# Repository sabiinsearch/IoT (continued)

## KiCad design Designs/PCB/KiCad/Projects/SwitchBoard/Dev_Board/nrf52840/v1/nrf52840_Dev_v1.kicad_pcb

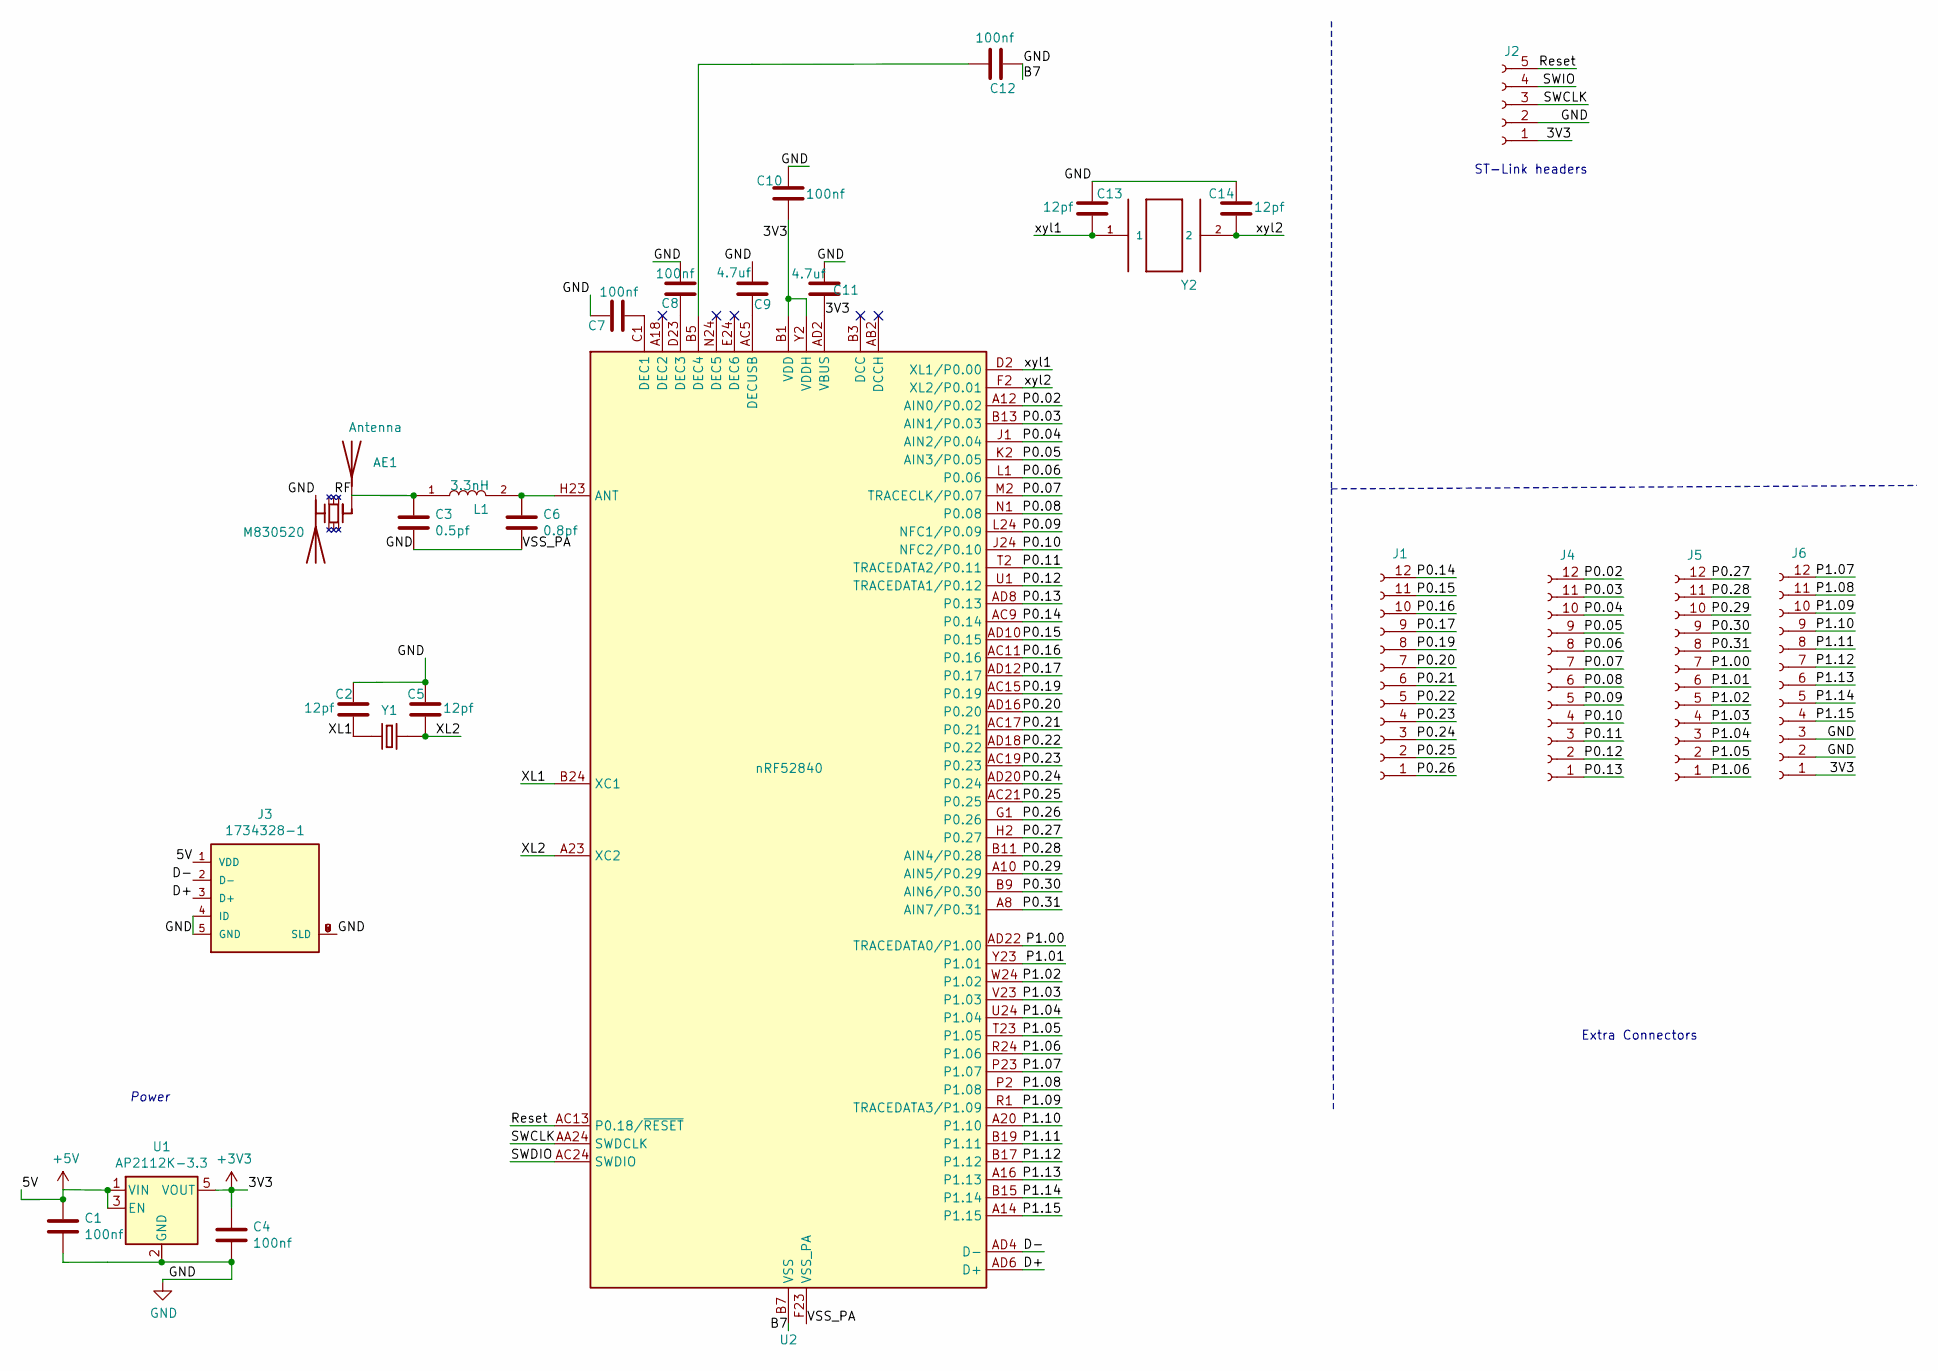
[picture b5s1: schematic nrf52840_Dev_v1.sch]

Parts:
AE1: Antenna; PinHeader_1x01_P2.54mm_Vertical
AE2: M830520
C1, C4, C7, C8, C10, C12: 100nf; C_0805_2012Metric
C2, C5, C13, C14: 12pf; C_0805_2012Metric
C3: 0.5pf; C_0805_2012Metric
C6: 0.8pf; C_0805_2012Metric
C9, C11: 4.7uf; C_0805_2012Metric
J1, J4, J5, J6: Conn_01x12_Female; PinHeader_1x12_P2.54mm_Vertical
J2: Conn_01x05_Female; Pin_Header_Straight_1x05_Pitch2.54mm
J3: 1734328-1; usb_mini_TE_1734328-1
L1: 3.3nH; L_0805_2012Metric
U1: AP2112K-3.3; SOT-23-5
U2: nRF52840; NRF52840-QIAA-R
Y1: ABM7-32.000MHZ-D2Y-T; XTAL_ABM7-32.000MHZ-D2Y-T; PARTREV 08.06.15
Y2: ABS07-32.768KHZ-7-1-T; XTAL320X150X90

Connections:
/3V3: C4.1, C10.1, C11.1, J2.1, J6.1, U1.5 (VOUT), U2.A22 (VDD), U2.AD2 (VBUS), U2.AD14 (VDD), U2.AD23 (VDD), U2.B1 (VDD), U2.W1 (VDD), U2.Y2 (VDDH)
/5V: C1.1, J3.1 (VDD), U1.1 (VIN), U1.3 (EN)
/B7: AE2.2 (PCB_Trace), C1.2, C2.1, C3.2, C4.2, C5.1, C6.2, C7.2, C8.2, C9.2, C10.2, C11.2, C12.1, C13.1, C14.1, J2.2, J3.4 (ID), J3.5 (GND), J3.6 (SLD), J3.7 (SLD), J3.8 (SLD), J3.9 (SLD), J6.2, J6.3, U1.2 (GND), U2.B7 (VSS), U2.EP (VSS), U2.F23 (VSS_PA)
/D+: J3.3 (D+), U2.AD6 (D+)
/D-: J3.2 (D-), U2.AD4 (D-)
/P0.02: J4.12, U2.A12 (AIN0/P0.02)
/P0.03: J4.11, U2.B13 (AIN1/P0.03)
/P0.04: J4.10, U2.J1 (AIN2/P0.04)
/P0.05: J4.9, U2.K2 (AIN3/P0.05)
/P0.06: J4.8, U2.L1 (P0.06)
/P0.07: J4.7, U2.M2 (TRACECLK/P0.07)
/P0.08: J4.6, U2.N1 (P0.08)
/P0.09: J4.5, U2.L24 (NFC1/P0.09)
/P0.10: J4.4, U2.J24 (NFC2/P0.10)
/P0.11: J4.3, U2.T2 (TRACEDATA2/P0.11)
/P0.12: J4.2, U2.U1 (TRACEDATA1/P0.12)
/P0.13: J4.1, U2.AD8 (P0.13)
/P0.14: J1.12, U2.AC9 (P0.14)
/P0.15: J1.11, U2.AD10 (P0.15)
/P0.16: J1.10, U2.AC11 (P0.16)
/P0.17: J1.9, U2.AD12 (P0.17)
/P0.19: J1.8, U2.AC15 (P0.19)
/P0.20: J1.7, U2.AD16 (P0.20)
/P0.21: J1.6, U2.AC17 (P0.21)
/P0.22: J1.5, U2.AD18 (P0.22)
/P0.23: J1.4, U2.AC19 (P0.23)
/P0.24: J1.3, U2.AD20 (P0.24)
/P0.25: J1.2, U2.AC21 (P0.25)
/P0.26: J1.1, U2.G1 (P0.26)
/P0.27: J5.12, U2.H2 (P0.27)
/P0.28: J5.11, U2.B11 (AIN4/P0.28)
/P0.29: J5.10, U2.A10 (AIN5/P0.29)
/P0.30: J5.9, U2.B9 (AIN6/P0.30)
/P0.31: J5.8, U2.A8 (AIN7/P0.31)
/P1.00: J5.7, U2.AD22 (TRACEDATA0/P1.00)
/P1.01: J5.6, U2.Y23 (P1.01)
/P1.02: J5.5, U2.W24 (P1.02)
/P1.03: J5.4, U2.V23 (P1.03)
/P1.04: J5.3, U2.U24 (P1.04)
/P1.05: J5.2, U2.T23 (P1.05)
/P1.06: J5.1, U2.R24 (P1.06)
/P1.07: J6.12, U2.P23 (P1.07)
/P1.08: J6.11, U2.P2 (P1.08)
/P1.09: J6.10, U2.R1 (TRACEDATA3/P1.09)
/P1.10: J6.9, U2.A20 (P1.10)
/P1.11: J6.8, U2.B19 (P1.11)
/P1.12: J6.7, U2.B17 (P1.12)
/P1.13: J6.6, U2.A16 (P1.13)
/P1.14: J6.5, U2.B15 (P1.14)
/P1.15: J6.4, U2.A14 (P1.15)
/RF: AE1.1, AE2.1 (FEED), C3.1, L1.1
/Reset: J2.5, U2.AC13 (P0.18/~RESET)
/SWCLK: J2.3, U2.AA24 (SWDCLK)
/SWDIO: U2.AC24 (SWDIO)
/SWIO: J2.4
/XL1: C2.2, U2.B24 (XC1), Y1.1
/XL2: C5.2, U2.A23 (XC2), Y1.2
/xyl1: C13.2, U2.D2 (XL1/P0.00), Y2.1
/xyl2: C14.2, U2.F2 (XL2/P0.01), Y2.2
unnamed: C6.1, L1.2, U2.H23 (ANT)
unnamed: C7.1, U2.C1 (DEC1)
unnamed: C8.1, U2.D23 (DEC3)
unnamed: C9.1, U2.AC5 (DECUSB)
unnamed: C12.2, U2.B5 (DEC4)

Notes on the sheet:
ST-Link headers
Power
Extra Connectors

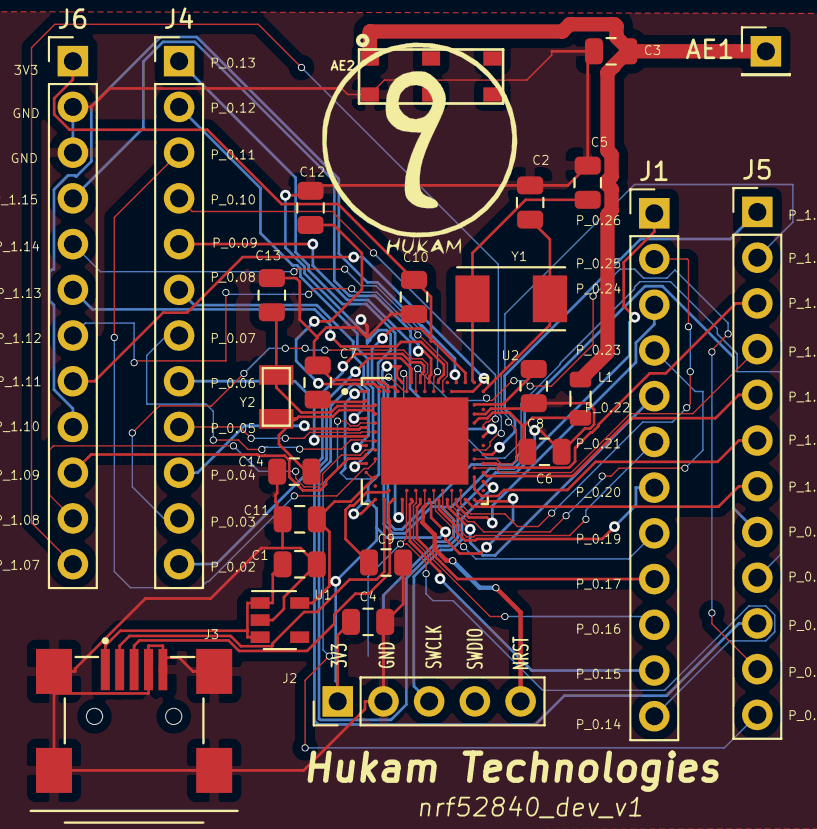
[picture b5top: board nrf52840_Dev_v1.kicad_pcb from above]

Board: 2 copper layers, 27 parts (0 on the bottom side), 62 nets.

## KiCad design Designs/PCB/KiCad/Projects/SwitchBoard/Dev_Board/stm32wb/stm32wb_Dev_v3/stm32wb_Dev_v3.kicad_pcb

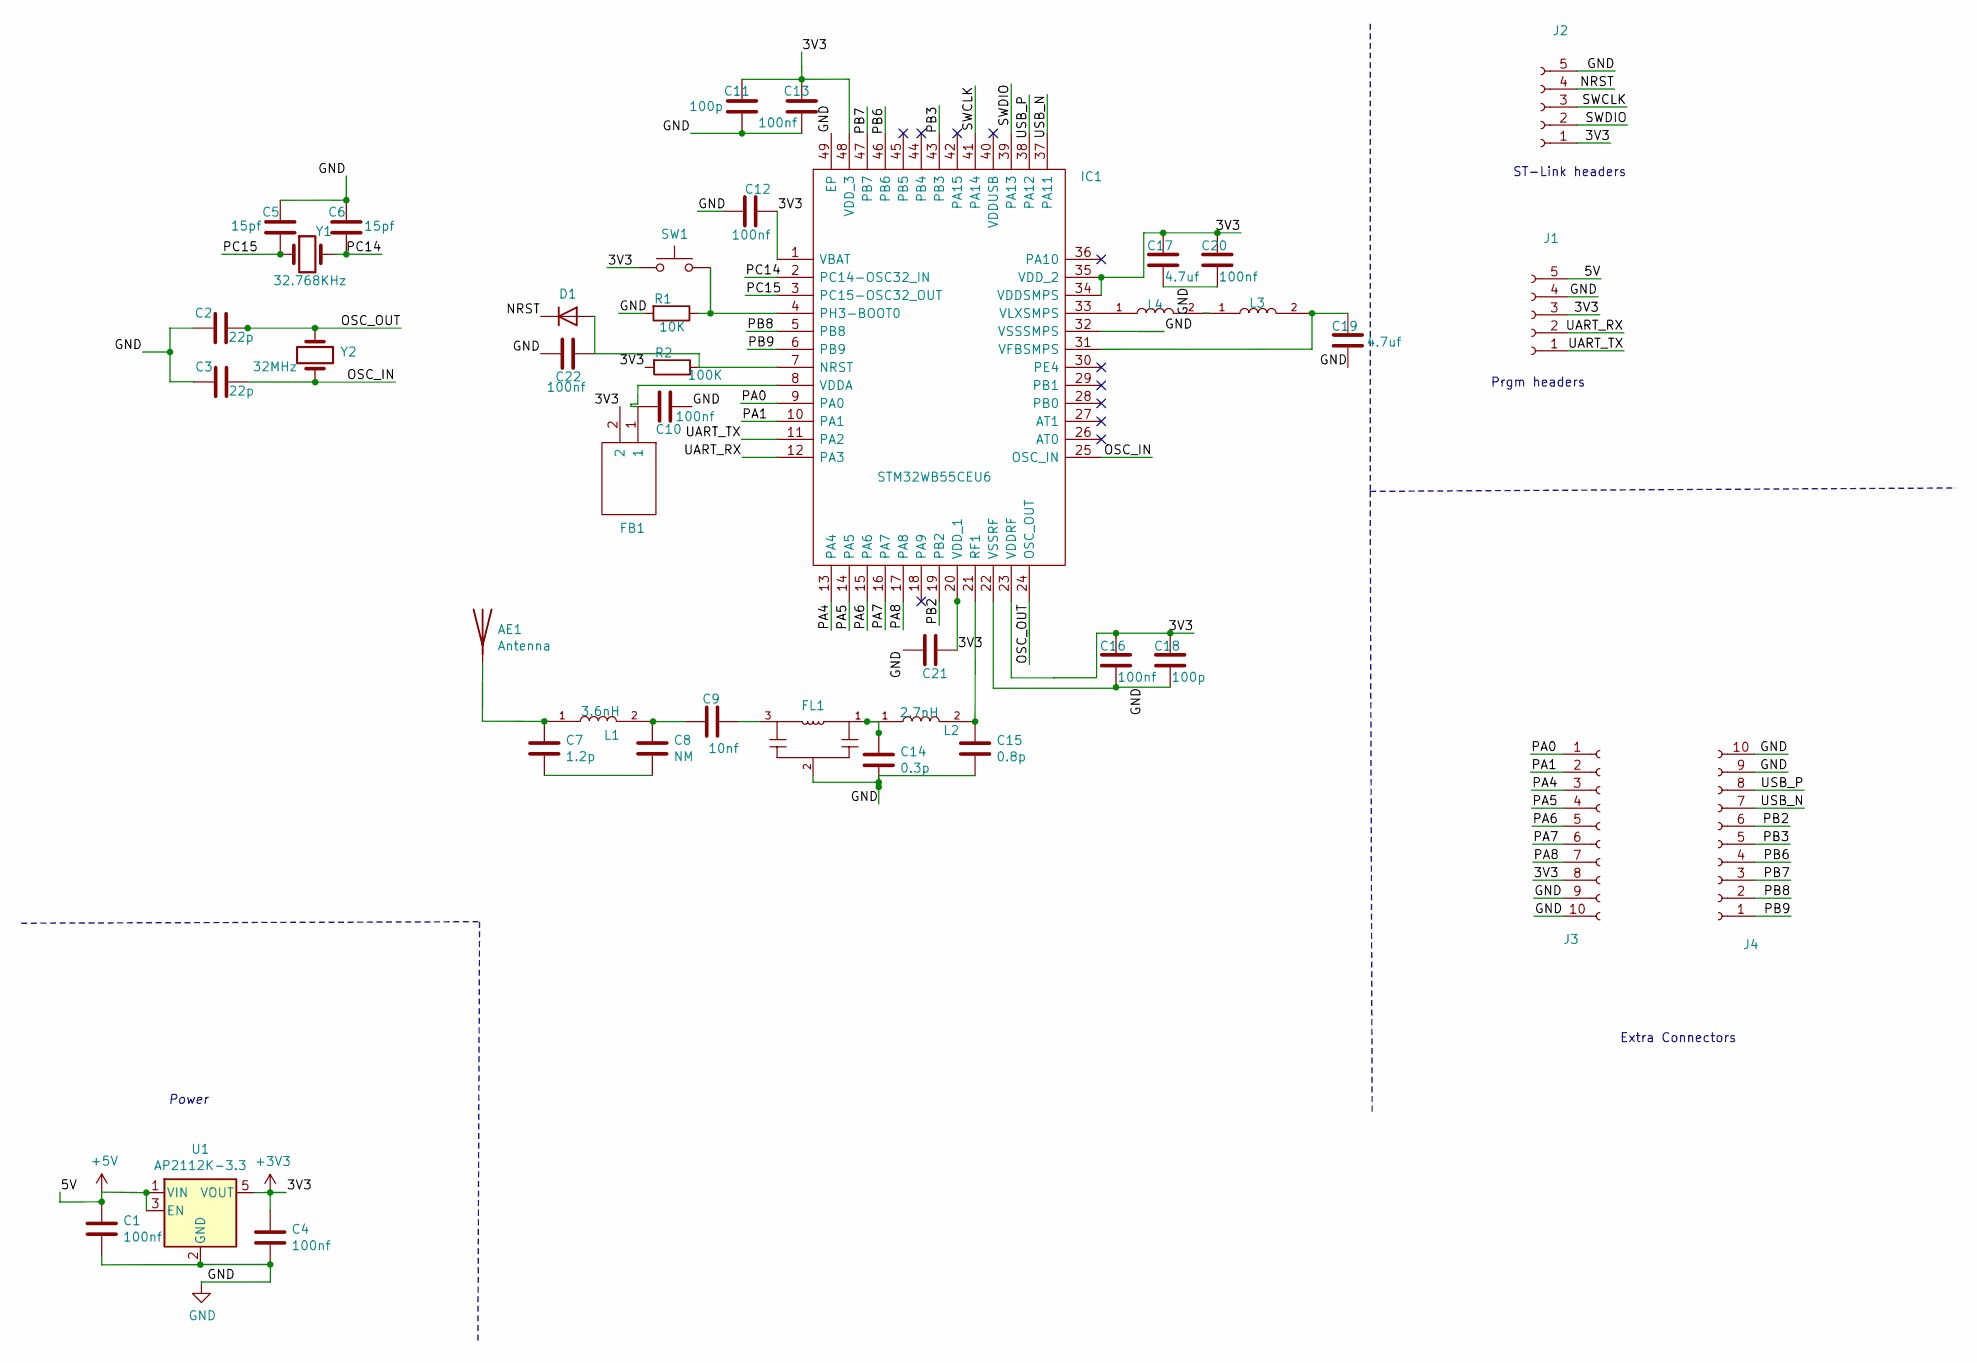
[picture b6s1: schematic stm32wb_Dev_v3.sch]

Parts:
AE1: Antenna; Pin_Header_Straight_1x01_Pitch2.54mm
C1, C4, C10, C12, C13, C16, C20: 100nf; C_0805
C2, C3: 22p; C_0805
C5, C6: 15pf; C_0805
C7: 1.2p; C_0805
C8: NM; C_0805
C9: 10nf; C_0805
C11, C18: 100p; C_0805
C14: 0.3p; C_0805
C15: 0.8p; C_0805
C17, C19: 4.7uf; C_1206_HandSoldering
C21: 100nf; C_0805_2012Metric
C22: 100nf; C_0805_2012Metric_Pad1.18x1.45mm_HandSolder
D1: BAT54K; D_1812_4532Metric
FB1: FCM1608KF-601T03; R_0805_2012Metric_Pad1.20x1.40mm_HandSolder; Manufacturer_Part_Number FCM1608KF-601T03
FL1: LFB182G45CGFD436; CAPC2012X135N
IC1: STM32WB55CEU6; QFN50P700X700X65-49N-D; Manufacturer_Part_Number STM32WB55CEU6; Mouser Part Number 511-STM32WB55CEU6
J1, J2: Conn_01x05_Female; Pin_Header_Straight_1x05_Pitch2.54mm
J3, J4: Conn_01x10_Female; PinHeader_1x10_P2.54mm_Vertical
L1: 3.6nH; L_0805_HandSoldering
L2: 2.7nH; L_0805_HandSoldering
L3: 10uH; L_0805_2012Metric
L4: 10nH; L_0805_2012Metric
R1: 10K; R_0805_2012Metric_Pad1.20x1.40mm_HandSolder
R2: 100K; R_0805_2012Metric_Pad1.20x1.40mm_HandSolder
SW1: SW_Push; SW_SPST_B3U-1000P
U1: AP2112K-3.3; SOT-23-5
Y1: 32.768KHz; Crystal_Round_d3.0mm_Vertical
Y2: 32MHz; Crystal_HC18-U_Vertical

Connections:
/3V3: C4.1, C11.1, C12.1, C13.1, C16.1, C17.1, C18.1, C20.1, C21.1, FB1.2, IC1.1 (VBAT), IC1.20 (VDD_1), IC1.23 (VDDRF), IC1.34 (VDDSMPS), IC1.35 (VDD_2), IC1.48 (VDD_3), J1.3, J2.1, J3.8, R2.2, SW1.1, U1.5 (VOUT)
/5V: C1.1, J1.5, U1.1 (VIN), U1.3 (EN)
/GND: C1.2, C2.2, C3.2, C4.2, C5.1, C6.1, C10.2, C11.2, C12.2, C13.2, C14.2, C15.2, C16.2, C17.2, C18.2, C19.2, C20.2, C21.2, C22.2, FL1.2, IC1.22 (VSSRF), IC1.32 (VSSSMPS), IC1.49 (EP), J1.4, J2.5, J3.9, J3.10, J4.9, J4.10, R1.2, U1.2 (GND)
/NRST: D1.1 (K), J2.4
/OSC_IN: C3.1, IC1.25 (OSC_IN), Y2.2
/OSC_OUT: C2.1, IC1.24 (OSC_OUT), Y2.1
/PA0: IC1.9 (PA0), J3.1
/PA1: IC1.10 (PA1), J3.2
/PA4: IC1.13 (PA4), J3.3
/PA5: IC1.14 (PA5), J3.4
/PA6: IC1.15 (PA6), J3.5
/PA7: IC1.16 (PA7), J3.6
/PA8: IC1.17 (PA8), J3.7
/PB2: IC1.19 (PB2), J4.6
/PB3: IC1.43 (PB3), J4.5
/PB6: IC1.46 (PB6), J4.4
/PB7: IC1.47 (PB7), J4.3
/PB8: IC1.5 (PB8), J4.2
/PB9: IC1.6 (PB9), J4.1
/PC14: C6.2, IC1.2 (PC14-OSC32_IN), Y1.2
/PC15: C5.2, IC1.3 (PC15-OSC32_OUT), Y1.1
/SWCLK: IC1.41 (PA14), J2.3
/SWDIO: IC1.39 (PA13), J2.2
/UART_RX: IC1.12 (PA3), J1.2
/UART_TX: IC1.11 (PA2), J1.1
/USB_N: IC1.37 (PA11), J4.7
/USB_P: IC1.38 (PA12), J4.8
unnamed: AE1.1, C7.1, L1.1
unnamed: C7.2, C8.2
unnamed: C8.1, C9.1, L1.2
unnamed: C9.2, FL1.3
unnamed: C10.1, FB1.1, IC1.8 (VDDA)
unnamed: C14.1, FL1.1, L2.1
unnamed: C15.1, IC1.21 (RF1), L2.2
unnamed: C19.1, IC1.31 (VFBSMPS), L3.2
unnamed: C22.1, D1.2 (A), IC1.7 (NRST), R2.1
unnamed: IC1.4 (PH3-BOOT0), R1.1, SW1.2
unnamed: IC1.33 (VLXSMPS), L4.1
unnamed: L3.1, L4.2

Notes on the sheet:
ST-Link headers
Prgm headers
Power
Extra Connectors

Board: 2 copper layers, 41 parts (24 on the bottom side), 38 nets, no tracks yet.

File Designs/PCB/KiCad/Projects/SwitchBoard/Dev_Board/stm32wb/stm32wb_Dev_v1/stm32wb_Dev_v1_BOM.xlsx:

Id | Designator | Value | Package | Quantity | Supplier and ref
1 | FL1 | LFB182G45CGFD436 | FIL_LFB182G45CGFD436 | 1
2 | IC1 | STM32WB55CEU6 | QFN50P700X700X65-49N-D | 1
3 | C19,C17 | 4.7uf | C_1206_HandSoldering | 2
4 | AE1 | Antenna | Pin_Header_Straight_1x01_Pitch2.54mm | 1
5 | C1,C4,C10,C12,C13,C16,C20 | 100nf | C_0805 | 7
6 | C2,C3 | 22p | C_0805 | 2
7 | C5,C6 | 10p | C_0805 | 2
8 | C7 | 1.2p | C_0805 | 1
9 | C8 | NM | C_0805 | 1
10 | C9 | 10nf | C_0805 | 1 |  |  |  | Available
11 | C11,C18 | 100p | C_0805 | 2 |  |  |  | Not Available
12 | C14 | 0.3p | C_0805 | 1
13 | C15 | 0.8p | C_0805 | 1
14 | J1,J2 | Conn_01x05_Female | Pin_Header_Straight_1x05_Pitch2.54mm | 2
15 | J3,J4 | Headers_01x12 | Pin_Header_Straight_1x12_Pitch2.54mm | 2
16 | L1 | 3.6nH | L_0805_HandSoldering | 1
17 | L2 | 2.7nH | L_0805_HandSoldering | 1
18 | L3 | 10nH | L_0805_HandSoldering | 1
19 | L4 | 10uH | L_0805_HandSoldering | 1
20 | R1 | 10K | R_0805 | 1
21 | SW1 | SW_Push | SW_SPST_B3U-1000P | 1
22 | U1 | AP2112K-3.3 | SOT-23-5 | 1
23 | Y1 | 32.768KHz | Crystal_Round_d3.0mm_Vertical | 1
24 | Y2 | 32MHz | Crystal_HC18-U_Vertical | 1

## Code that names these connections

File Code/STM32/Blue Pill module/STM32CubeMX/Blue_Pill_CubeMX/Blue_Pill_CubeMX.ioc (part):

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PC15-OSC32_OUT.Mode=LSE-External-Oscillator
PA6.Mode=Full_Duplex_Master
PA7.Mode=Full_Duplex_Master
PD1-OSC_OUT.Mode=HSE-External-Oscillator
Mcu.UserName=STM32F103C6Tx
PA10.Mode=Multiprocessor_communication
PA11.Mode=Device
PD0-OSC_IN.Signal=RCC_OSC_IN
PC14-OSC32_IN.Signal=RCC_OSC32_IN
RCC.SYSCLKSource=RCC_SYSCLKSOURCE_PLLCLK
PD1-OSC_OUT.Signal=RCC_OSC_OUT
PA3.Mode=Multiprocessor_communication
PA9.Mode=Multiprocessor_communication
PA12.Signal=USB_DP
PB9.Mode=Master
PA9.Signal=USART1_TX
PB6.Signal=I2C1_SCL
PB6.Mode=I2C
PC15-OSC32_OUT.Signal=RCC_OSC32_OUT
PD0-OSC_IN.Mode=HSE-External-Oscillator
PA5.Signal=SPI1_SCK
board=custom
PC14-OSC32_IN.Mode=LSE-External-Oscillator
PB7.Signal=I2C1_SDA
Mcu.Name=STM32F103C(4-6)Tx
PA2.Signal=USART2_TX
RCC.SYSCLKFreq_VALUE=48000000
Mcu.Package=LQFP48
PB9.Signal=CAN_TX
PA6.Signal=SPI1_MISO
PA12.Mode=Device
PB7.Mode=I2C
PA11.Signal=USB_DM
PA10.Signal=USART1_RX
PB8.Mode=Master
PA2.Mode=Multiprocessor_communication
PB8.Signal=CAN_RX
PA3.Signal=USART2_RX
PA5.Mode=Full_Duplex_Master
PA7.Signal=SPI1_MOSI

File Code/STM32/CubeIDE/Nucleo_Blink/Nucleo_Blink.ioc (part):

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Mcu.Name=STM32WB55RGVx
Mcu.Package=VFQFPN68
Mcu.UserName=STM32WB55RGVx
PA11.Mode=Device
PA11.Signal=USB_DM
PA12.Mode=Device
PA12.Signal=USB_DP
PA13.GPIOParameters=GPIO_Label
PA13.GPIO_Label=JTMS
PA13.Mode=Trace_Asynchronous_SW
PA13.Signal=SYS_JTMS-SWDIO
PA14.GPIOParameters=GPIO_Label
PA14.GPIO_Label=JTCK
PA14.Mode=Trace_Asynchronous_SW
PA14.Signal=SYS_JTCK-SWCLK
PB0.GPIOParameters=GPIO_Label
PB0.GPIO_Label=LD2 [Green Led]
PB0.Signal=GPIO_Output
PB1.GPIOParameters=GPIO_Label
PB1.GPIO_Label=LD3 [Red Led]
PB1.Signal=GPIO_Output
PB3.GPIOParameters=GPIO_Label
PB3.GPIO_Label=JTDO
PB3.Mode=Trace_Asynchronous_SW
PB3.Signal=SYS_JTDO-SWO
PB5.GPIOParameters=GPIO_Label
PB5.GPIO_Label=LD1 [Blue Led]
PB5.Signal=GPIO_Output
PB6.GPIOParameters=GPIO_PuPd,GPIO_Label
PB6.GPIO_Label=STLINK_RX
PB6.GPIO_PuPd=GPIO_PULLUP
PB6.Mode=Asynchronous
PB6.Signal=USART1_TX
PB7.GPIOParameters=GPIO_PuPd,GPIO_Label
PB7.GPIO_Label=STLINK_TX
PB7.GPIO_PuPd=GPIO_PULLUP
PB7.Mode=Asynchronous
PB7.Signal=USART1_RX
PC13.Mode=SYS_WakeUp1
PC13.Signal=SYS_WKUP2
PC14-OSC32_IN.Mode=LSE-External-Oscillator
PC14-OSC32_IN.Signal=RCC_OSC32_IN
PC15-OSC32_OUT.Mode=LSE-External-Oscillator
PC15-OSC32_OUT.Signal=RCC_OSC32_OUT
PC4.GPIOParameters=GPIO_Label
PC4.GPIO_Label=B1 [Push Button]
PC4.Signal=GPIO_Input
PD0.GPIOParameters=GPIO_Label
PD0.GPIO_Label=B2 [Push Button]
PD0.Signal=GPIO_Input
PD1.GPIOParameters=GPIO_Label
PD1.GPIO_Label=B3 [Push Button]
PD1.Signal=GPIO_Input
RCC.HSE_VALUE=32000000
RCC.SYSCLKFreq_VALUE=32000000
RCC.SYSCLKSource=RCC_SYSCLKSOURCE_HSE
board=P-NUCLEO-WB55-Nucleo
boardIOC=true

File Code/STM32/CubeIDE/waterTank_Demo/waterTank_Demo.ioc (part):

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Mcu.Name=STM32F103C(8-B)Tx
Mcu.Package=LQFP48
Mcu.UserName=STM32F103C8Tx
PA10.Mode=Asynchronous
PA10.Signal=USART1_RX
PA13.Mode=Serial_Wire
PA13.Signal=SYS_JTMS-SWDIO
PA14.Mode=Serial_Wire
PA14.Signal=SYS_JTCK-SWCLK
PA4.Mode=NSS_Signal_Hard_Output
PA4.Signal=SPI1_NSS
PA5.Mode=Full_Duplex_Master
PA5.Signal=SPI1_SCK
PA6.Mode=Full_Duplex_Master
PA6.Signal=SPI1_MISO
PA7.Mode=Full_Duplex_Master
PA7.Signal=SPI1_MOSI
PA9.Mode=Asynchronous
PA9.Signal=USART1_TX
PB10.Signal=GPIO_Input
PB11.Signal=GPIO_Output
PB15.Signal=GPIO_Output
PD0-OSC_IN.Mode=HSE-External-Oscillator
PD0-OSC_IN.Signal=RCC_OSC_IN
PD1-OSC_OUT.Mode=HSE-External-Oscillator
PD1-OSC_OUT.Signal=RCC_OSC_OUT
RCC.SYSCLKFreq_VALUE=72000000
RCC.SYSCLKSource=RCC_SYSCLKSOURCE_PLLCLK
board=custom

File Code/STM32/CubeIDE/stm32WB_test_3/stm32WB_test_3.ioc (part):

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Mcu.Name=STM32WB50CGUx
Mcu.Package=UFQFPN48
Mcu.UserName=STM32WB50CGUx
PA1.Signal=GPIO_Input
PA10.Mode=Asynchronous
PA10.Signal=USART1_RX
PA11.Signal=GPIO_Output
PA12.Signal=GPIO_Output
PA13.Mode=Serial_Wire
PA13.Signal=SYS_JTMS-SWDIO
PA14.Mode=Serial_Wire
PA14.Signal=SYS_JTCK-SWCLK
PB0.GPIOParameters=GPIO_Label
PB0.GPIO_Label=LED (Green)
PB0.Signal=GPIO_Output
PB5.Signal=GPIO_Output
PB6.Mode=Asynchronous
PB6.Signal=USART1_TX
PC14-OSC32_IN.Mode=LSE-External-Oscillator
PC14-OSC32_IN.Signal=RCC_OSC32_IN
PC15-OSC32_OUT.Mode=LSE-External-Oscillator
PC15-OSC32_OUT.Signal=RCC_OSC32_OUT
RCC.HSE_VALUE=32000000
RCC.SYSCLKFreq_VALUE=32000000
RCC.SYSCLKSource=RCC_SYSCLKSOURCE_HSE
board=custom

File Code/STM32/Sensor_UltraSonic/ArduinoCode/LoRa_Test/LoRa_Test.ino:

/*
 circuitdigest.com
 Sample STM32 Blink Program for Blue Pill board
 */

// #include <Arduino.h>
#include <ArduinoJson.h>
//#include <SPI.h>              // include libraries
#include <LoRa_STM32.h>

//#define LED_BUILTIN PC13
#define echoPin PA8 // attach pin D2 Arduino to pin Echo of HC-SR04
#define trigPin PA9 //attach pin D3 Arduino to pin Trig of HC-SR04

const int csPin = PA4;          // LoRa radio chip select
const int resetPin = PC13;       // LoRa radio reset
const int irqPin = PA0;         // change for your board; must be a hardware interrupt pin

String outgoing;              // outgoing message

byte msgCount = 0;            // count of outgoing messages
byte localAddress = 0xBB;     // address of this device
byte destination = 0xFF;      // destination to send to
long lastSendTime = 0;        // last send time
int interval = 1000;          // interval between sends


void sendMessage(String outgoing) {
  LoRa.beginPacket();                   // start packet
  // LoRa.write(destination);              // add destination address
  // LoRa.write(localAddress);             // add sender address
  // LoRa.write(msgCount);                 // add message ID
  // LoRa.write(outgoing.length());        // add payload length
  LoRa.print(outgoing);                 // add payload
  LoRa.endPacket();                     // finish packet and send it
  // msgCount++;                           // increment message ID
}

// returns the distance (cm)
void measureDistance() {
  digitalWrite(trigPin, LOW);
  delayMicroseconds(2);
  digitalWrite(trigPin, HIGH); // We send a 10us pulse
  delayMicroseconds(10);
  // delay(1);
  digitalWrite(trigPin, LOW);

  uint32_t duration = pulseIn(echoPin, HIGH, 25000); // We wait for the echo to come back, with a timeout of 20ms, which corresponds approximately to 3m
  // long duration = pulseIn(echoPin, HIGH);

  // pulseIn will only return 0 if it timed out. (or if echoPin was already to 1, but it should not happen)
  // If we timed out
  if(duration == 0) {
    pinMode(echoPin, OUTPUT); // Then we set echo pin to output mode
    digitalWrite(echoPin, LOW); // We send a LOW pulse to the echo pin
    delayMicroseconds(200);
    pinMode(echoPin, INPUT); // And finaly we come back to input mode
  }

  // float distance = (duration/2) / 29.1; // We calculate the distance (sound speed in air is aprox. 291m/s), /2 because of the pulse going and coming
  float distance = duration * 0.034 / 2;
  // float distance = duration / 58.138f;

  // String payload = "{\"type\":\"" BOARD_TYPE "\", \"uniqueId\":\"" +BOARD_ID+"\", \"deviceIndex\":1, \"deviceValue\": " +String(sw1Val)+"}";
  String payload;
  StaticJsonDocument<200> data;
//  JsonObject& jsonOut = dataJsonBuffer.createObject();
  data["distance"] = distance;
  String output="Hello World";
  serializeJson(data, output);
  sendMessage(output);
}

// the setup function runs once when you press reset or power the board
void setup() {
  // initialize digital pin PC13 as an output.
  //pinMode(LED_BUILTIN, OUTPUT);
  pinMode(trigPin, OUTPUT); // Sets the trigPin as an OUTPUT
  pinMode(echoPin, INPUT); // Sets the echoPin as an INPUT

  LoRa.setPins(csPin, resetPin, irqPin);// set CS, reset, IRQ pin

  if (!LoRa.begin(433E6)) {             // initialize ratio at 915 MHz
    // Serial.println("LoRa init failed. Check your connections.");
    while (true);                       // if failed, do nothing
  }

}

// the loop function runs over and over again forever
void loop() {
 // digitalWrite(LED_BUILTIN, HIGH);   // turn the LED on (HIGH is the voltage level)
  delay(500);
  //sendMessage("Hello World...");           // wait for a second
  measureDistance();
 // digitalWrite(LED_BUILTIN, LOW);    // turn the LED off by making the voltage LOW
  delay(500);              // wait for a second
}

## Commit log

2020-06-05 addd IoT rep
2020-06-05 Shifted to New Repository (IoT)
2020-06-05 Switch Board with four switches
2020-07-10 update structure
2020-07-10 Importing EasyEda Desgns in KiCad
2020-07-11 LPC schematic
2020-07-19 PCB_Drawing
2020-07-19 Schematic
2020-07-19 Sensor_PCB.pdf
2020-07-19 Schematic.pdf
2020-07-19 PCB Layout
2020-07-19 Gerber Files
2020-07-19 Gerber
2020-10-14 Update on 14-10-20 at 0542 hrs
2020-10-31 Add LoRa test rig
2022-04-12 learnings
2022-04-29 update chnanges before system uninstall
2022-04-29 update before uninstall ubuntu
2022-05-01 just check commit from vscode
2022-05-04 too many changes
2022-05-04 include PIO libraries
2022-05-04 Into of Water Level Receiver
2022-05-23 update in nrf
2022-05-29 EnergyMonitoring
2022-05-29 update_29-05-2022
2022-07-08 adding WiFiManager
2022-07-09 Added folder include for c_cpp_properties.json err
2022-07-09 disabling Wifi
2022-07-09 test to merge
2022-07-09 test to check synch
2022-07-09 for testing sync
2022-07-09 testing
2022-07-09 commit message
2022-07-10 Communication library added
2022-07-10 Adding ReceiverBoard_lib
2022-07-11 Adding Energy_Monitoring_lib
2022-07-11 some cust libraries working
2022-07-11 Setting Cust Libs
2022-07-11 Clean recieverBoard lib
2022-07-11 Some more cleaning of Cust_lib
2022-07-12 updating after including cutom libraries
2022-07-12 Added to getBoard_ID
2022-07-13 Calibrating Energy Monitoring
2022-07-13 undergoing Energy Monitoring
2022-07-14 Energy Calculation
2022-07-17 update Energy Monitoring
2022-07-17 Adding Matter example for learning
2022-07-17 add Rainmaker application
2022-07-17 Rain Maker
2022-08-06 update to ESP
2022-08-07 Code seggregation
2022-08-08 adding mqtt
2022-08-08 update mqtt
2022-08-09 added connection manager
2022-08-09 added connnectionManager
2022-08-09 added connectionManager
2022-08-09 added appManager & connectionManager
2022-08-16 functionality with Managers
2022-08-16 adding Managers
2022-08-16 adding Managers with functionality
2022-08-17 changes in energy Monitoring
2022-08-17 working a bit energyMonitoring
2022-08-17 Managers Working
2022-08-17 Energy Monitoring Working
2022-08-17 Application Working (except mqtt)
2022-08-17 update config (under process)
2022-08-17 Extra Libs removed
2022-08-17 Extra Libraries removed
2022-08-17 added Tank level indicators (except MQTT)
2022-08-17 Changes in Design
2022-09-11 editing design
2022-09-13 Energy Monitoring
2022-11-19 change in design
2023-07-31 new Design files
2023-08-08 update_design
2023-09-01 Design_Dev_c2652_v1
2023-09-06 updatge c_cpp_properties.json
2023-09-15 updatge c_Dev_board_v1_BOM.xls
2023-09-21 updated BOM
2023-10-11 update_design files
2023-10-12 update design files
2024-01-03 deleted
